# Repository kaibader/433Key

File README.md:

# LoRa Breakout Board for RFM95/RFM96 and SX1276/SX1278 Modules

This repository contains KiCad design files for a breadboard-friendly breakout board that supports various LoRa modules, such as the **HopeRF RFM95/RFM96** or Semtech **SX1276/SX1278**-based modules like the HPD13A and G-NiceRF LoRa1276-C1.

## Features

| Top View | Bottom View |
| -------- | ----------- |
|  |  |

- Supports **HopeRF RFM95/RFM96** and other pin-compatible LoRa modules.
- Designed to fit standard breadboards for easy prototyping.
- Simple SPI-based communication with microcontrollers.

## Schematic Overview

The breakout board includes the following key components and connections:

### 1. **LoRa Module**
   - This module, based on the SX1276 transceiver, handles LoRa communication at 868 MHz or 915 MHz.
   - It communicates with the microcontroller via the **SPI interface** (SCK, MOSI, MISO, NSS pins).
   - Additional **DIO pins (DIO0-DIO5)** are exposed, allowing the module to send interrupts or general-purpose I/O signals.
   - **Antenna**: The RFM9x is connected to an external antenna via an SMA connector for wireless communication.

### 2. **SPI Interface**
   - The SPI interface is used to connect the RFM9x to a microcontroller, with signals for **MISO, MOSI, SCK, NSS (SEL)**, and a **RESET** pin.
   - This enables the module to send and receive data through standard SPI communication.

### 3. **DIO Pin Connector**
   - The board provides access to the **DIO0-DIO5 pins**, which are general-purpose input/output pins for signaling and interrupt control. These can be connected to a microcontroller for event-driven handling of LoRa transmissions.

### 4. **Antenna Connection (SMA)**
   - The **SMA connector** is used to attach an external antenna, which is crucial for enabling long-range LoRa communication.

### 5. **Power Supply and Decoupling Capacitors**
   - The board operates at **+3.3V** and includes two decoupling capacitors:
     - **C1 (100nF)** and **C2 (4.7uF)** help filter out noise and stabilize the power supply to ensure proper operation of the LoRa module.
   - These capacitors prevent voltage fluctuations from affecting the module's performance, especially during transmission.

### 6. **Reset Circuit**
   - The **RESET pin** is connected to a 100k pull-up resistor **(R2)**, and another 100k resistor **(R1)** is used to control the accessibility (via **SEL**) of the module.
   - This allows external control for reinitializing the module as needed.

## Pin-Compatible LoRa Modules

This breakout board is designed to be compatible with the **HopeRF RFM9x** series and the following pin-compatible alternatives:

1. **HopeRF RFM95** (by HopeRF):
   - A widely used LoRa transceiver module that supports long-range, low-power wireless communication.
   - **Manufacturer**: [HopeRF](https://www.hoperf.com).

2. **HPD13A** (by HPD Technology):
   - A pin-compatible and shielded alternative to the RFM95, based on the SX1276 transceiver.
   - **Manufacturer**: [HPD Technology](http://www.hpdtek.com).

3. **G-NiceRF LoRa1276-C1** (by NiceRF):
   - A pin-compatible module using the same SX1276 chip as the HPD13A, designed for similar wireless communication applications.
   - **Manufacturer**: [NiceRF](https://www.nicerf.com).

Feel free to inform me about other alternatives that are available and pin-compatible.

## License

This project is licensed under the **Creative Commons Attribution 4.0 International (CC BY 4.0)**. See the [LICENSE](https://creativecommons.org/licenses/by/4.0/) page for details.

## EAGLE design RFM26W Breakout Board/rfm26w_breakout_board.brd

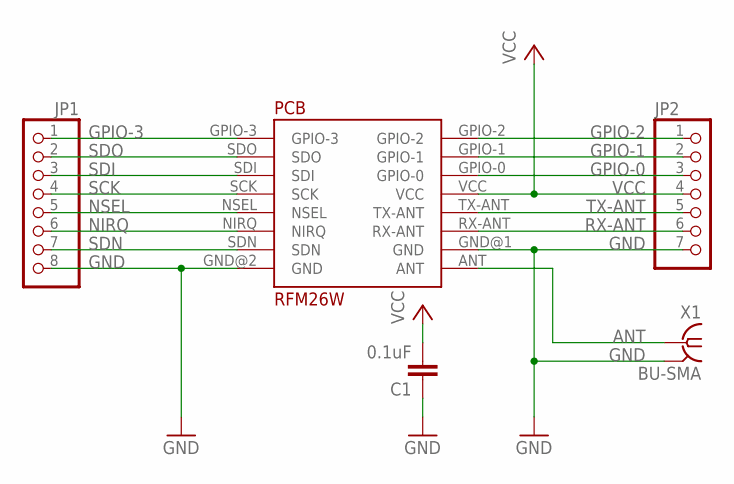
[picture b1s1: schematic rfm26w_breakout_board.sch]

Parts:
C1: 0.1uF; C0805K
JP1: PINHD-1X8; 1X08
JP2: PINHD-1X7; 1X07
PCB: RFM26W
X1: BU-SMA; BU-SMA-V

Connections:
ANT: PCB.ANT, X1.1
GND: C1.1, JP1.8, JP2.7, PCB.GND@1 (GND), PCB.GND@2 (GND), X1.2, X1.3 (2), X1.4 (2), X1.5 (2)
GPIO-0: JP2.3, PCB.GPIO-0
GPIO-1: JP2.2, PCB.GPIO-1
GPIO-2: JP2.1, PCB.GPIO-2
GPIO-3: JP1.1, PCB.GPIO-3
NIRQ: JP1.6, PCB.NIRQ
NSEL: JP1.5, PCB.NSEL
RX-ANT: JP2.6, PCB.RX-ANT
SCK: JP1.4, PCB.SCK
SDI: JP1.3, PCB.SDI
SDN: JP1.7, PCB.SDN
SDO: JP1.2, PCB.SDO
TX-ANT: JP2.5, PCB.TX-ANT
VCC: C1.2, JP2.4, PCB.VCC

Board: 2 copper layers, 5 parts (0 on the bottom side), 15 nets, no tracks yet.

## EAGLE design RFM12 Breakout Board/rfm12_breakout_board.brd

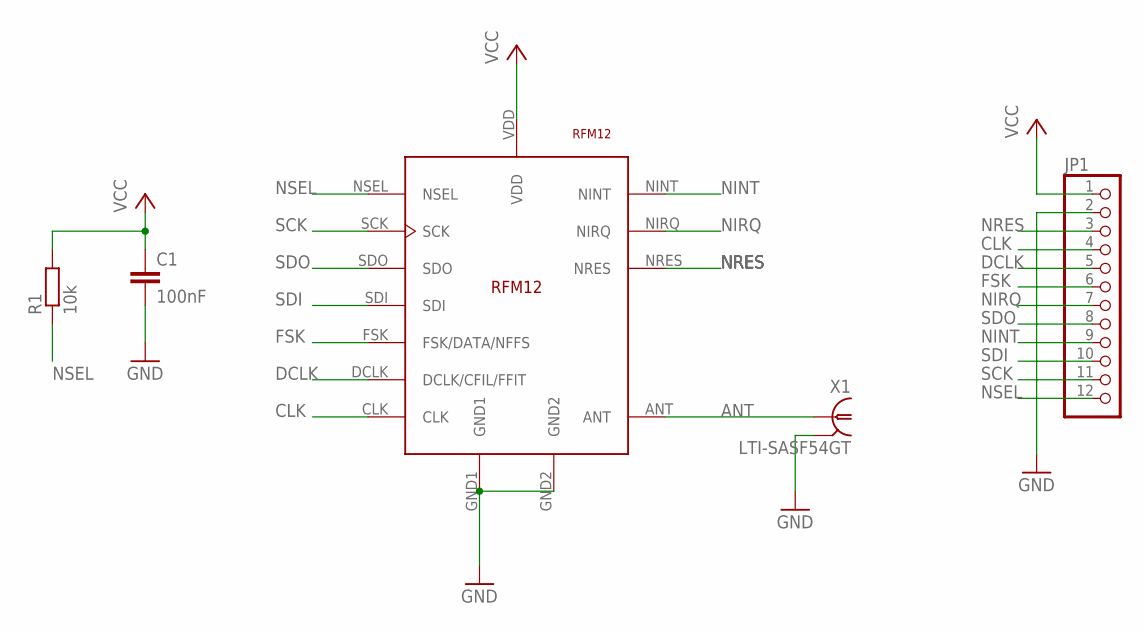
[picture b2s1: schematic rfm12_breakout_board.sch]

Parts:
C1: 100nF; C0805
JP1: PINHD-1X12/90; 1X12/90
R1: 10k; M0805
U$1: RFM12
X1: LTI-SASF54GT

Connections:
ANT: U$1.ANT, X1.1
CLK: JP1.4, U$1.CLK
DCLK: JP1.5, U$1.DCLK (DCLK/CFIL/FFIT)
FSK: JP1.6, U$1.FSK (FSK/DATA/NFFS)
GND: C1.2, JP1.2, U$1.GND1, U$1.GND2, X1.2, X1.3 (2), X1.4 (2), X1.5 (2)
NINT: JP1.9, U$1.NINT
NIRQ: JP1.7, U$1.NIRQ
NRES: JP1.3, U$1.NRES
NSEL: JP1.12, R1.1, U$1.NSEL
SCK: JP1.11, U$1.SCK
SDI: JP1.10, U$1.SDI
SDO: JP1.8, U$1.SDO
VCC: C1.1, JP1.1, R1.2, U$1.VDD

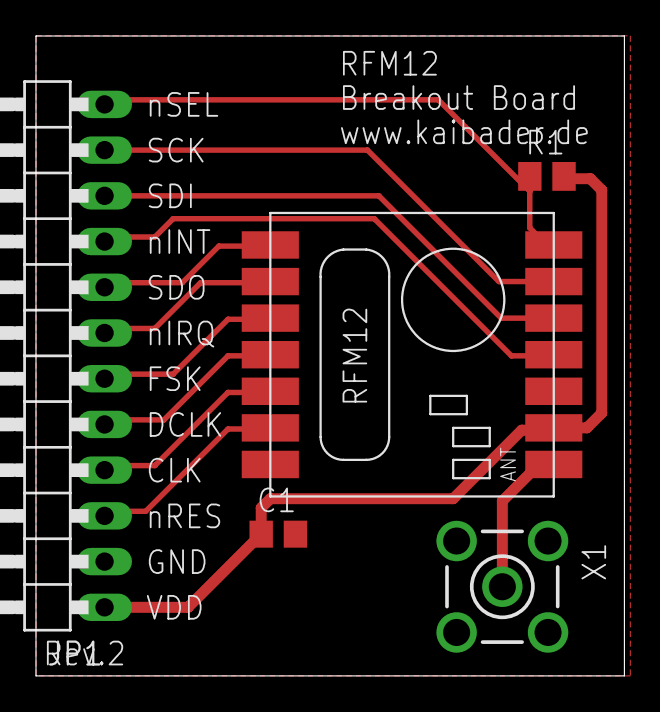
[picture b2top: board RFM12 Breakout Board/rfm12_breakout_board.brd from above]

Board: 2 copper layers, 32.7 x 35.5 mm, 5 parts (0 on the bottom side), 13 nets.

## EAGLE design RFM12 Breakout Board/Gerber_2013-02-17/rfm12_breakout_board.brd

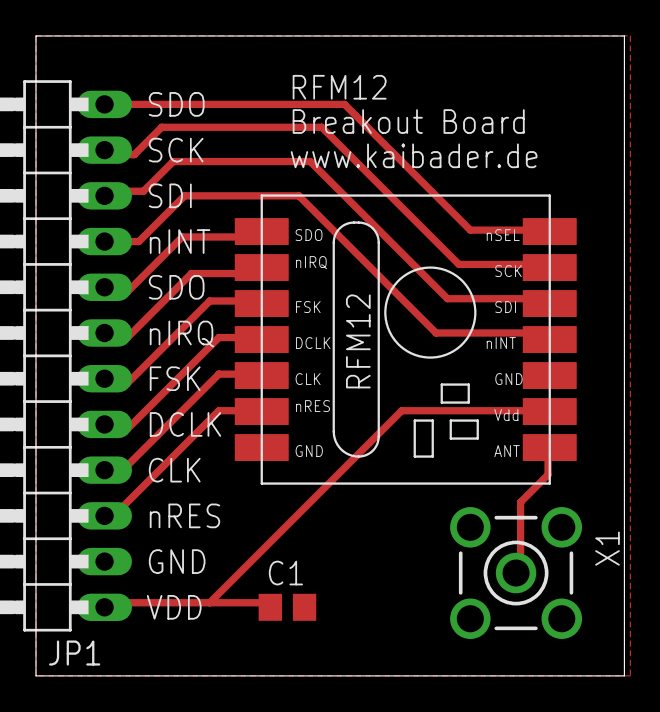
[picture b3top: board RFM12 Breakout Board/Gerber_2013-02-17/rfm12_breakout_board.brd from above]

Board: 2 copper layers, 32.7 x 35.5 mm, 4 parts (0 on the bottom side), 13 nets.

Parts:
C1: 100nF; C0805
JP1: 1X12/90
U$1: RFM12
X1: LTI-SASF54GT

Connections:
CLK: JP1.4, U$1.5
DCLK: JP1.5, U$1.4
FSK: JP1.6, U$1.3
GND: C1.2, JP1.2, U$1.7, U$1.10, X1.2, X1.3, X1.4, X1.5
unnamed: U$1.8, X1.1
NINT: JP1.9, U$1.11
NIRQ: JP1.7, U$1.2
NRES: JP1.3, U$1.6
NSEL: JP1.12, U$1.14
SCK: JP1.11, U$1.13
SDI: JP1.10, U$1.12
SDO: JP1.8, U$1.1
VCC: C1.1, JP1.1, U$1.9

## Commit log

2013-10-22 Initial commit. Created an ignore list.
2015-10-11 Added files for the RFM12 Breakout Board.
2015-10-11 Updated the ignore list.
2015-10-11 Added Gerber files.
2015-10-11 Routed the RFM26W Breakout Board.
2015-10-11 Layout update
2015-10-11 Some clean-up.
2015-10-11 Fixed the font line width to 6 mil.
2015-10-11 Done some clean-up.
2015-10-11 Layout updates.
2015-10-11 Added a RFM26W Breakout Board design.
2017-02-09 Switched the project frame to KiCad
2017-02-09 Revert "Switched the project frame to KiCad"
2017-02-09 Clean-up
2022-11-18 Converted the RFM12 and RFM26W Breakout Board Projects from EagleCAD to KiCAD.
2022-11-18 Added Specification PDFs
2022-11-18 Renamed Specification Folder to Documentation
2022-11-27 Added RFM95/RFM96 and RFM69W Breakout Boards.
2022-12-04 Updated the RFM69W and RFM95W/RFM96W board layouts.
2022-12-04 Generated Gerber files.
2024-09-07 LoRa Breakout Board Revision 2
    - Shifted the focus of the repository towards the new LoRa breakout board design.
    - Moved the old designs into a 'Deprecated' folder.
    - Added a ReadMe (Markdown).
    - Added module documentation.
2024-09-07 Clean-up. Removed an obsolete file.
2024-09-07 Added a README for the deprecated designs.
